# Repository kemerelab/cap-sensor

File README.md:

# Capacitive sensor
## Theory
Capacitive sensing relies on, as the name suggests, the capacitance of the involved circuit. Capacitance, in turn, is the ability to store electrical charge under an applied voltage, which is employed by components termed capacitors. Clasically, capacitors can be visualized as two conductor plates separated by some distance $d$; the capacitance of these "parallel plate capacitors" is then governed by the equation:

$$
\displaystyle
C = \dfrac{Q}{V} = \epsilon \dfrac{A}{d}
$$

where $Q$ is the electrical charge stored on conductor plate; $V$ is the voltage applied to the capacitor; $\epsilon$ is the dielectric constant of the medium separating the plates; $A$ is the area of each plate; and $d$ is the distance between the plates.

Once charged after application of a voltage across the conductor plates (by, for example, a battery), the capacitor will similarly discharge across another component of a circuit if provided the opportunity. For example, consider the simple RC circuit below.

When connected to the battery, the capacitor with capacitance $C$ will store an amount of charge $Q$ after equilibrating at the battery voltage $V_B$ (position 1). If the circuit is disconnected from the battery (position 2), then an electric current will flow from the positively charged capacitor plate across the resistor to ground. The time-dependent voltage across the capacitor, $V_C$ follows a well-known exponential decay:

$$
\displaystyle
V(t) = V_B e^{-\frac{t}{\tau}}
$$

where $\tau = RC$ is known as the time constant of the circuit and is given by the product of the resistance and capacitance. (Similarly, reflecting the equation across the time axis gives the time-dependence for charging the capacitor.)

Lastly, it can be shown that for capacitors placed in parallel in an electrical circuit, the capacitance of the circuit is the sum of the individual capacitances of each capacitor:

$$
\displaystyle
C_{tot} = C_1 + C_2 + \cdots + C_n
$$

In other words, capacitance is additive in parallel.

How do these principles apply to capacitive sensing? Let's suppose that we have the RC circuit similar to the one above, except that we have an additional wire that connects the positive terminal to a conductive plate (i.e. one-half of a parallel plate capacitor). As some object object, say a finger, approaches this plate, it can form the other (negative) plate to generate an additional parallel plate capacitor. Moreover, if this object is connected to a large electrical reservoir, like a human body, it is in effect "virtually grounded", which functionally acts as if connected to the circuit ground, and thereby makes the new capacitor lie in parallel with the known capacitor. Consequently, because capacitance adds in parallel, the new capacitance of the circuit will have increased. (The exact amount is not important, as we will see.) (If placed directly between the plates of a large capacitor, the sensed object can also affect capacitance by altering the dielectric field; however, this principle is not applicable to this setup.)

How do we measure this change in capacitance? By relying on the time constant of the RC circuit! After charging the capacitor(s), the battery is disconnected, and the rate of voltage decay across the capacitor can be measured. As the sensed object (finger) approaches the sensor (plate), the overall capacitance of circuit increases. Because the resistance is fixed, the time constant is only modified by the change in capacitance and consequently increases as well. Thus, the time for the voltage to decrease by a given amount is prolonged. (We could similarly measure the time to charge the capacitor and see that it is also prolonged with increased capacitance.)

Although the voltage change during discharge theoretically follows an exponential decay, it often not necessary to model the voltage decay as such, nor to solve for $\tau$ directly. As mentioned above, the change in capacitance will alter the time to reach certain voltage thresholds during discharge in a predictable direction. The codebase on which this sensor is based counts the number of cycles on the microcontroller until logic LOW is reached as a rough estimate of this duration. An increase or decrease in this output reflects an increase or decrease, respectively, of the circuit capacitance.

The implementation of capacitive sensing for lick detection is shown below. An RC circuit is run on a microcontroller that toggles between charging (position 1) and discharging (position 2) the integrated capacitor ($C_1$). Additionally, a wire connects the positive terminal to the metallic lick spout, which functions as one end of a capacitor. During licking, as the tongue approaches the lick spout, it functions as the other end of the capacitor ($C_2$), thereby increasing the capacitance of the RC circuit and, consequently, the time constant, a detectable change as noted above. The tongue is connected to the animal's body and perhaps, depending on the specifics of the experimental rig, the material on which the animal is sitting; in either case, the electrical storage capacity is large enough relative to the circuit that it functions as a virtual ground for the "other" plate of the capacitor. (Although the tongue does touch the lick spout during licking, the specifics of whether the sensor is detecting proximity or contact is less important. For instance, even when in contact with the lick spout directly, the intervening reward solution and saliva, as well as the epithelial layer of the tongue, can be modeled as the dielectric material separating the capacitive plates for a capacitor, albeit a potentially leaky one.) 

The change in charging or discharging time in the RC circuit is detected by a script running on the microcontroller. Both a "send" pin and a "receive" pin are initially set to logic LOW in an output state. The send pin is then switched to logic HIGH ($V_s$), while the receive pin is switched to an input state. A counter tracks the number of clock cycles until the voltage of the recieve pin ($V_r$) reaches the logic HIGH state (i.e. capacitor charging). Once the capacitor is fully charged, the reverse occurs to track capacitor discharging. Full implementation details can be found at the developers' repository [here](https://github.com/PaulStoffregen/CapacitiveSensor).

## Overview of sensor
### Hardware
The capacitive sensing components are integrated onto a small printed circuit board (PCB) that was designed using Autodesk EAGLE (v9.5). Files pertaining to the PCB, including design files and parts lists, can be found in the `pcb` directory. A schematic is shown below.

The sensor uses a microcontroller (Adafruit M0 Trinket; component **1** in diagram) that gathers the sensing input, runs the lick detection firmware (more below), and outputs the lick signal. It requires a 3.3V power source (but is tolerant up to 6V) that may be provided either directly through the micro USB hub or through the audio jack (**4**) via an external source that may be switched on or off (**5**). The components of the sensing circuit are the thru-hole for a wire connected to the lickspout (**8**); a fixed (**2**) and variable (**6**) resistor (comprising $R$ in circuit diagram above); a stabilizing capacitor (**3**, comprising $C_1$ in diagram above); and, if needed, a thru-hole for a separate ground connection (**9**). The voltage from this modified RC circuit is fed as input into a pin on the microcontroller in order to run lick detection firmware. The sensitivity of lick detection can be adjusted manually by tuning the specified variable resistor (**7**).

The output signal is sent via a different microcontroller pin to the signal component (ring of tip-ring-sleeve, or TRS, composition) of the audio jack. Additionally, the red status LED turns on whenever a lick is detected (i.e. HIGH signal output).

### Firmware
The firmware that runs lick detection can be found under the `firmware` directory. Three different scripts (`capacitiveSensor`, `capacitiveSensorFilter`, `capacitiveSensorVariable`) run a common algorithm with slightly different variants. The input voltage from the lick detection circuit is fed to the [CapacitiveSensor](https://github.com/PaulStoffregen/CapacitiveSensor) library to provide a rough estimate of the time constant, which is returned as a unitless number. Larger values mean larger time constants and a higher likelihood of a lick occurring. Once the value exceeds a set threshold, a lick is detected and the signal output set to HIGH. That threshold can be fixed in the firmware (`capacitiveSensor.ino`) or modified within a range by the variable resistor knob on the PCB (`capacitiveSensor.ino`). Lastly, the time constant values instead may be first fed through a filter (`capacitiveSensorFilter.ino`; moving average or median filter) in order to smooth the input signal. Explanations of the parameters within and use of each script is provided below in `Usage Guide`.

## Installation
The PCB design files and a list of hardware components can be found in the `pcb` directory. Once acquired, the surface-mount (R1, C1) and through-hole (trimpots, power switch, audio jack) components should be soldered to the PCB. Pin headers should be soldered to the PCB and to the microcontroller, which can be then be mounted onto the board.

Next, an insulated wire should be measured and cut to the desired length, noting that it will be connected to the through-hole labeled `SENSE` at one end and to the lickspout at the other. The length of wire should allow for enough slack to avoid pulling on either component but avoid excess slack, which will increase the noise of the input (as it essentially functions as an antenna). We suggest first soldering the wire to the lickspout and then soldering the other end to the through-hole.

After all components have been soldered to the board, the microcontroller should be programmed with the firmware of choice. A computer containing the firmware files can be connected to the microcontroller via its micro USB hub. Either the Arduino IDE (which can be downloaded [here](https://www.arduino.cc/en/software)) or software with Arduino integration (e.g. VS Code) may be used to upload the firmware. A detailed guide to installing the IDE and uploading scripts can be found [here](https://learn.adafruit.com/adafruit-trinket-m0-circuitpython-arduino/arduino-ide-setup). The three scripts that may be uploaded are `capacitiveSensor.ino`, `capacitiveSensorFilter.ino`, and `capacitiveSensorVariable.ino`. If using `capacitiveSensorFilter.ino`, the binaries for the files located in `firmware/libaries` must be compiled to a location within `firmware` (such as `firmware/bin`).

Once the hardware and firmware installation is complete, the microcontroller may be powered by either the audio jack via an external power supply or the microUSB port. In either case, it requires a 3.3 V power supply but is tolerant up to 6 V. If the audio jack is used, the power and ground should be connected to the tip and sleeve of the cable, respectively. Note that if the microUSB port is connected to a host computer, then power will automatically switch over even if an external power source is connected to the audio jack.

The output signal may be harnessed from either pin 3 on the microcontroller or the ring component of the audio jack. The output is logic LOW when no lick is detected and logic HIGH when a lick is detected.

## Usage guide
The sensor may be quickly tested by touching the peripheral end of the sense wire or the component to which it is connected (e.g. a lickspout). The red status LED on the microcontroller should turn on when the component is touched and only when it is touched. If the status light does not illuminate, first attempt to modify the settings below before proceeding to the Troubleshooting section.

As with many sensors, there is a trade-off between the sensitivity (capturing lick events) and specificity (ignoring noise) of detection, of which the sensor has two primary means of adjusting: via hardware and via firmware.

The knob on the variable resistor (trimpot) labeled `R CIRCUIT` tunes the resistance of the RC circuit that underlies lick detection. By turning it clockwise, the resistance is increased, which in turn increases the sensitivity of the detector. (Specifically, the time constant is increased via the $R$ in $\tau=RC$; any changes in the capacitance $C$ are then amplified in the read-out value on which detection is thresholded.) Larger values may reliably detect proxmity rather than touch if desired.

Each script has modifiable parameters that govern its sensitivity to lick detection. The most straightforward is the detection threshold, which, using output values from the underlying `CapacitiveSensor` library, delineates between the baseline state (below threshold) and lick state (above threshold). The detection threshold may be hard-coded (in `capacitiveSensor.ino`) or adjusted via the knob on the trimpot labeled `THRESH` (in `capacitiveSensorVariable.ino` and `capacitiveSensorFilter.ino`). In the latter case, the range of values corresponding to the knob position are set by the low and high limits coded in the script. All scripts are specify the sampling rate, which corresponds to the frequency with which sensor values are sampled and compared to threshold. If filters are employed (`capacitiveSensorFilter.ino`), several other parameters specify various properties of the filter that affect detection speed and accuracy; these are explained in further detail in the iPython notebook found at `testing/python/filters.ipynb`. The full list of parameters is displayed in the table below.

| parameter | variable name | description | script(s) |
|-----------|---------------|-------------|-----------|
| sampling rate | `sampleRate` | rate of sensor value acquisition | `capactiveSensor`, `capactiveSensorVariable`, `capactiveSensorFilter` |
| threshold | `th`, `thresh` | value above which the output signal is HIGH | `capactiveSensor`, `capactiveSensorVariable`, `capactiveSensorFilter` |
| lower limit of threshold | `th_low`, `thresh_low` | threshold value when `THRESH` set to lowest setting | `capactiveSensorVariable`, `capactiveSensorFilter` |
| upper limit of threshold | `th_high`, `thresh_high` | threshold value when `THRESH` set to highest setting | `capactiveSensorVariable`, `capactiveSensorFilter` |
| algorithm sensitivity | `sensitivity` | number of cycles to estimate time constant | `capactiveSensorFilter` |
| threshold type* | `method` | specifies threshold based on absolute values or z-score | `capactiveSensorFilter` |
| coefficient of signal value* | `alpha` | contribution of signal to filter buffer stats | `capactiveSensorFilter` |
| filter duration* | `tFilter` | duration of filter buffer (seconds) | `capactiveSensorFilter` |
| downsample factor* | `k` | specifies period for updating filter buffer |  `capactiveSensorFilter` |

*See `testing/python/filters.ipynb` for details.

## Troubleshooting
**General debugging**: Each firmware script is programmed to output debugging values every iteration as listed in the table below. When the microcontroller is connected to a host computer via its microUSB hub, these values can be accessed either through the serial monitor or by piping the output to a text file. Each row represents values for a given iteration, and values within an iteration are separated by a whitespace.

| firmware | default frequency | values | | | | |
|---|---|---|---|---|---|---|
`capactiveSensor` | 30 kHz | timestamp (microseconds) | sensor value | | | |
`capacitiveSensorVariable` | 30 kHz | timestamp (microseconds) | sensor value | detection threshold | | |
`capacitiveSensorFilter` | 0.2 kHz | timestamp (microseconds) | sensor value | detection threshold | buffer mean | output |

**Error occurs while attempting to upload firmware**: Make sure that both the Adafruit and the Arduino libraries for the SAMD21 boards are installed in board config (see tutorial [here](https://learn.adafruit.com/adafruit-trinket-m0-circuitpython-arduino/arduino-ide-setup)).

**Microcontroller not recognized by computer (i.e. does not mount)**: Try resetting the microcontroller by (1) double clicking the reset button on the microcontroller to enter bootloader mode (red LED should flash on and off), and then (2) dragging the appropriate UF2 file into the newly mounted controller (see [here](https://learn.adafruit.com/introducing-itsy-bitsy-m0/uf2-bootloader-details) for details).

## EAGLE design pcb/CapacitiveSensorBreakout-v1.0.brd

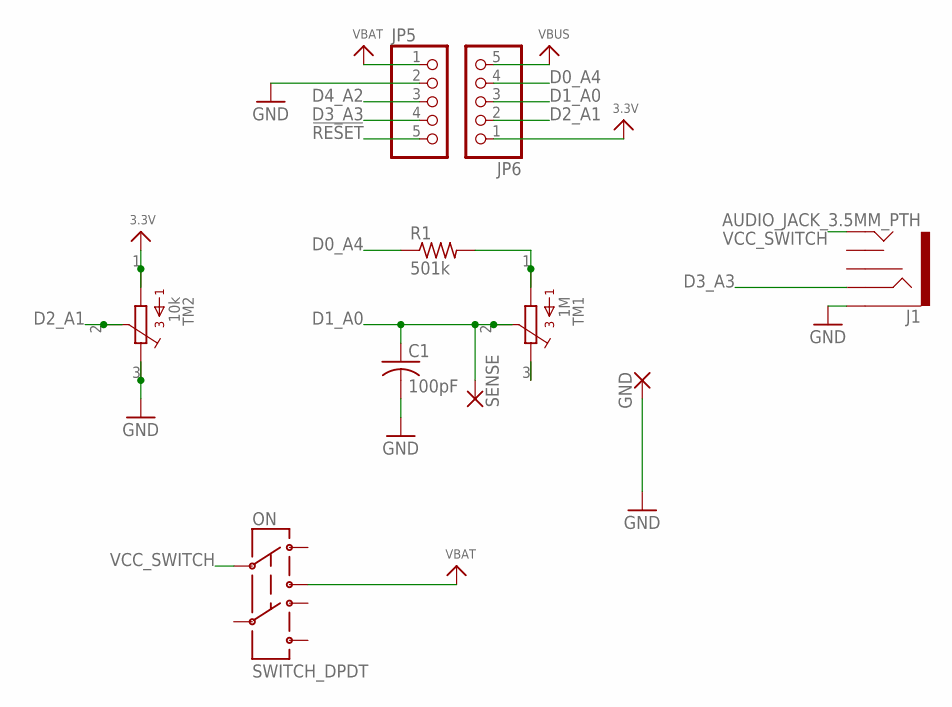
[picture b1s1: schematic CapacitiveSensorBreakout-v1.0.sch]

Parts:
C1: 100pF; C0603
GND: 1,6/0,8
J1: AUDIO_JACK_3.5MM_PTH; AUDIO-JACK
JP5, JP6: HEADER-1X576MIL; 1X05_ROUND_76
ON: SWITCH_DPDT; JS_DPDT_TH
R1: 501k; R0603
SENSE: 1,6/0,8
TM1: 1M; 3386-MULTI
TM2: 10k; 3386-MULTI

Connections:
3.3V: JP6.1, TM2.1, TM2.4
!RESET: JP5.5
D0_A4: JP6.4, R1.1
D1_A0: C1.1, JP6.3, SENSE.1, TM1.2, TM1.5
D2_A1: JP6.2, TM2.2, TM2.5
D3_A3: J1.RING, JP5.4
D4_A2: JP5.3
GND: C1.2, GND.1, J1.SLEEVE, JP5.2, TM2.3, TM2.6
unnamed: TM1.3, TM1.6
unnamed: R1.2, TM1.1, TM1.4
VBAT: JP5.1, ON.3
VBUS: JP6.5
VCC_SWITCH: J1.TIP, ON.2

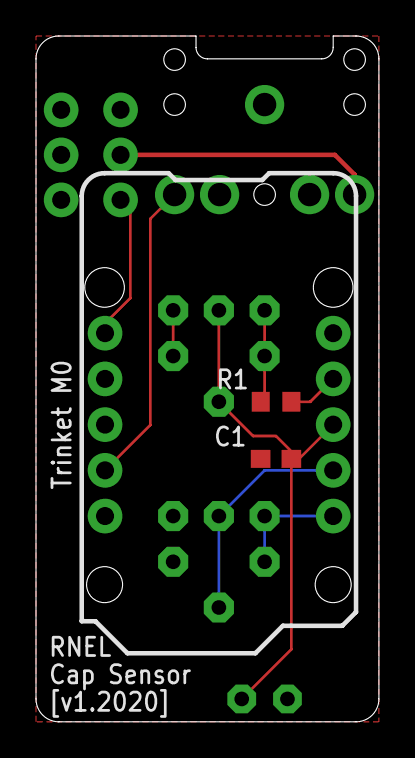
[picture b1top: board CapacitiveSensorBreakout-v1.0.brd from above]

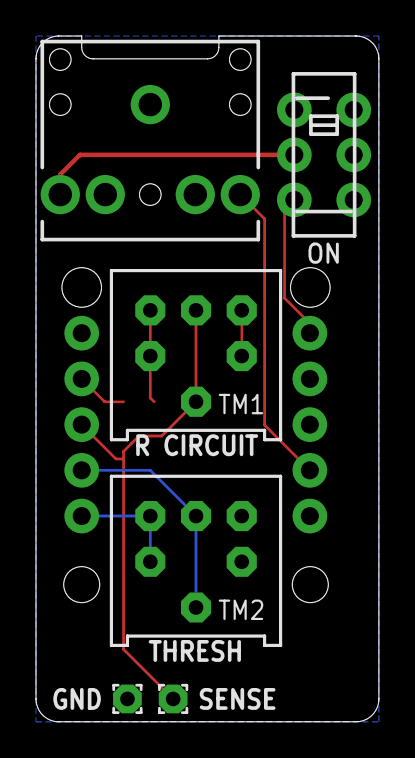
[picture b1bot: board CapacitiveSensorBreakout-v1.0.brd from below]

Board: 2 copper layers, 19.1 x 38.1 mm, 10 parts (6 on the bottom side), 10 nets.

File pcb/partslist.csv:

Name,Part,Value,Manufacturer,Product ID,Description
capacitor (0603 SMD),C1,100pF,-,-,provides baseline capacitance in sensor circuit
resistor (0603 SMD),R1,501k,-,-,provides baseline resistance in sensor circuit
trimpot,TM1,1M,Bourns,3386P-1-105TLF,tunes resistance in sensor circuit
trimpot,TM2,5k,Bourns,3386P-1-502TLF,tunes detection threshold in firmware
audio jack,J1,3.5 mm,CUI Devices,SJ1-3523N,"carries power, signal output, and ground"
power switch,SWITCH,DPDT,C&K,JS202011CQN ,power switch for PCB
microcontroller,JP5/JP6,Trinket M0,Adafruit,3500,runs firmware for signal detection

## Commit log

2021-04-15 reorganized directory structure
2021-04-15 updated gitignore to reflect new directories
2021-04-15 added breakout board files
2021-04-21 added correct output pin for Trinket M0
2021-05-14 updated filtered version to be compatible with Trinket M0 breakout board
2021-06-17 restructured data tree; added experimental data to debug
2021-06-23 minor fixes
2021-06-23 updated moving average to include downsampling, numerical threshold, low start latency
2021-08-17 new experimental and filtered data files
2021-08-17 minor fixes and updates
2021-08-17 bug fix relating to firmware reset
2021-08-17 experimental data analysis of appropriate filters for estimating baseline
2022-08-23 cleaned up plots
2023-11-13 updated documentation
2023-11-13 minor display fix

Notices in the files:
parts and their libraries:
microbuilder: This work is placed in the public domain, and may be freely used for commercial and non-commercial work with the following conditions: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
SparkFun-Connectors: Licensing: Creative Commons ShareAlike 4.0 International - https://creativecommons.org/licenses/by-sa/4.0
